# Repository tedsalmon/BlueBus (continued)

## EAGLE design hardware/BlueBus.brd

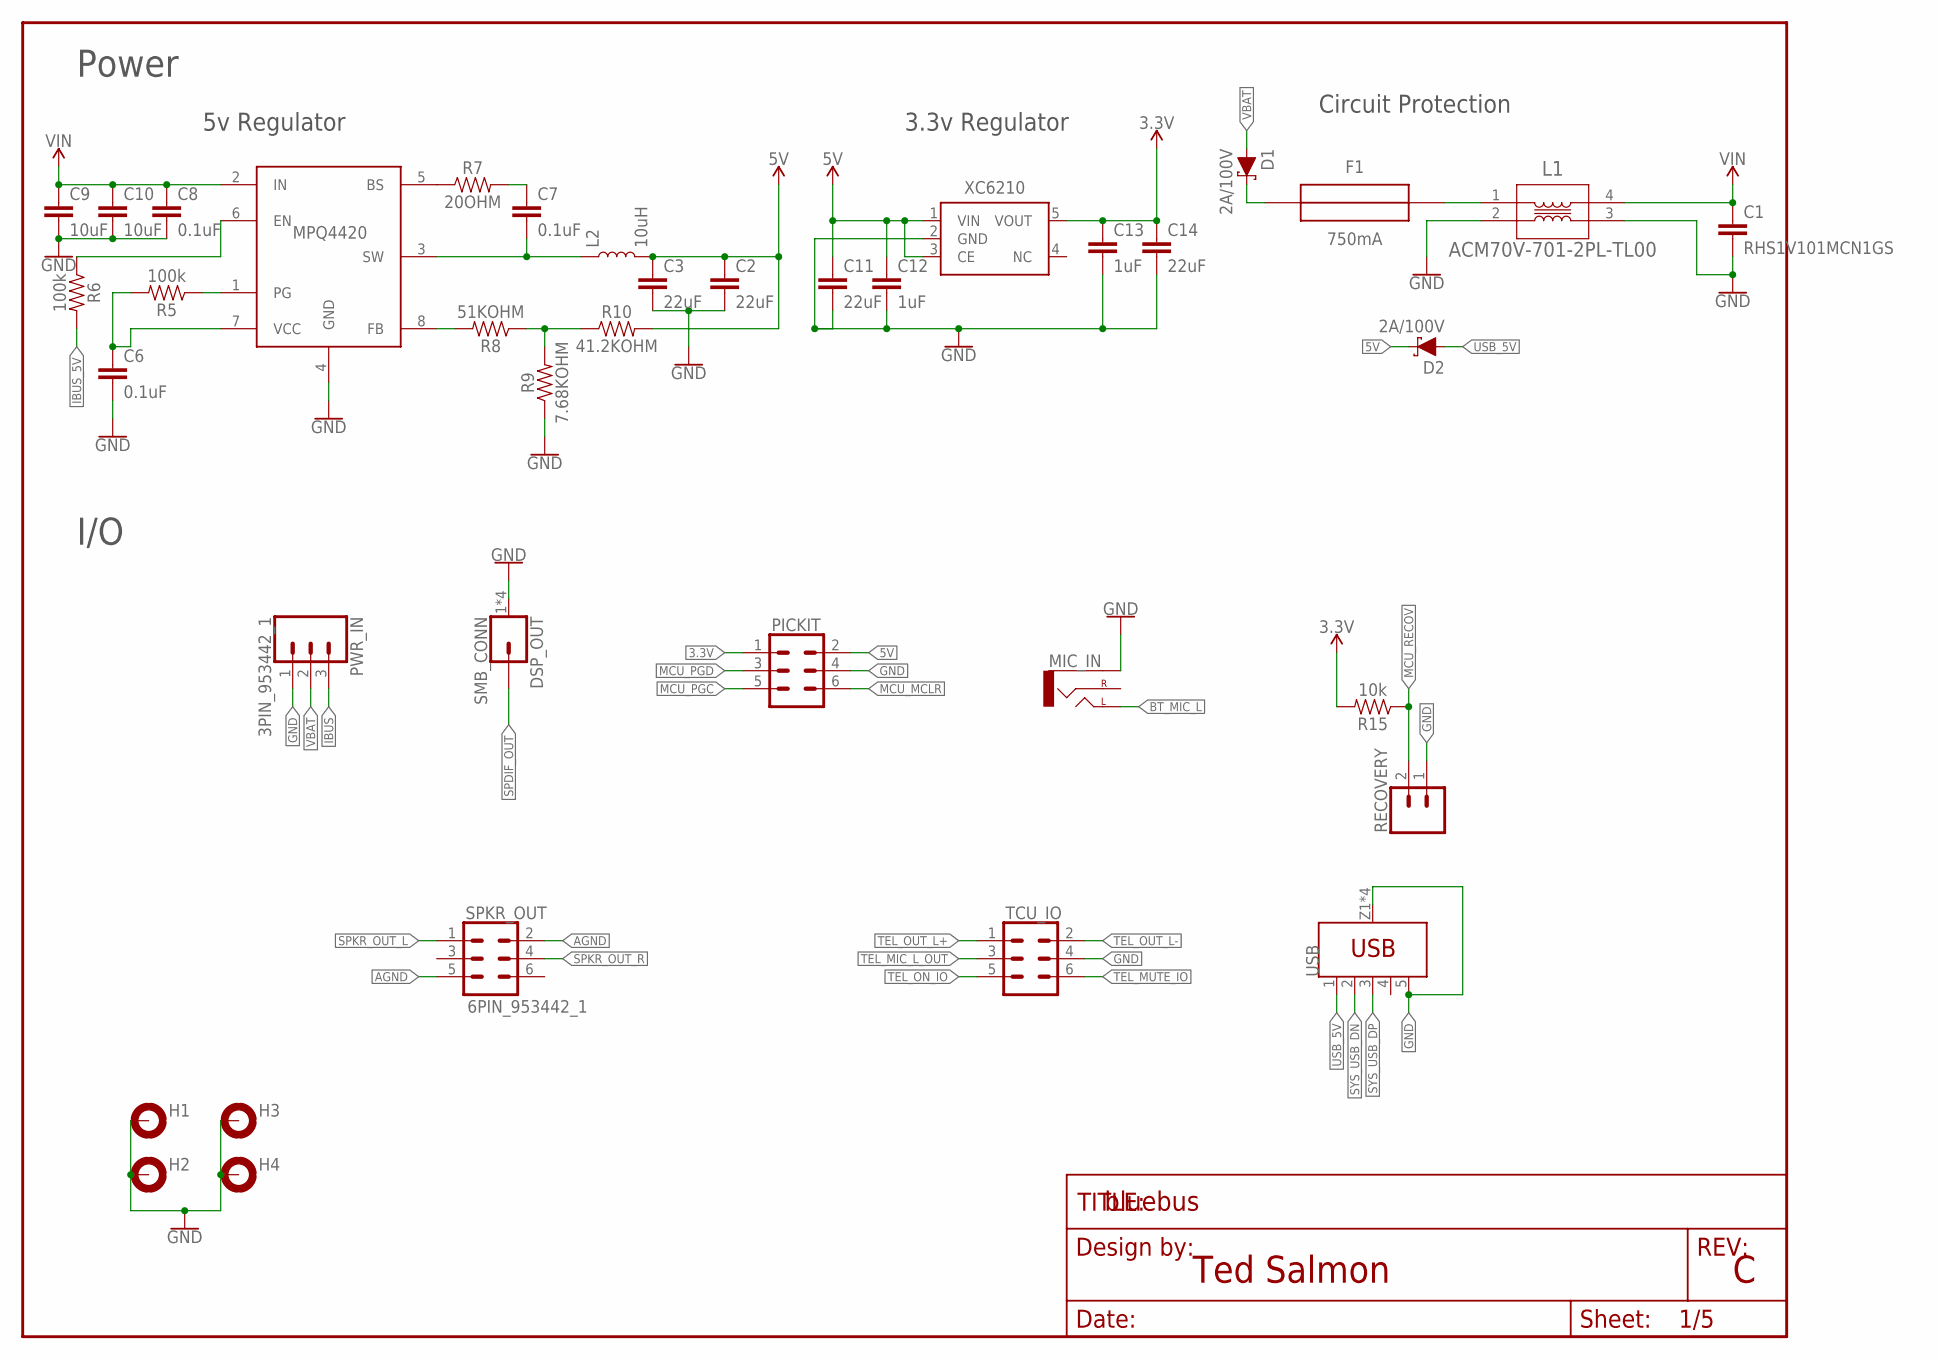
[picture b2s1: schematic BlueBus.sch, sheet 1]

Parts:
C1: RHS1V101MCN1GS
C2, C3, C11, C14: 22uF; 0805
C6, C7, C8: 0.1uF; 0805
C9, C10: 10uF; 1206
C12, C13: 1uF; 0805
D1, D2: 2A/100V; SOD123
DSP_OUT: SMB_CONN; MOLEX_SMB
F1: 750mA; LITTLEFUSE
FRAME1: FRAME-LETTER; DUMMY
H1, H2, H3, H4: 2,2-PAD; 2.2-PAD
L1: ACM70V-701-2PL-TL00
L2: 10uH; MPL-SE5040
MIC_IN: AUDIO-CUI-SJ-3523-SMT; AUDIO-CUI-SJ-352X-SMT
MPQ4420: MPQ4420; TSOT23-8
PICKIT: 6PIN_JUMPER; 2X3
PWR_IN: 3PIN_953442_1; TE_MQS_3PIN
R5, R6: 100k; 0805
R7: 20OHM; 0805
R8: 51KOHM; 0805
R9: 7.68KOHM; 0805
R10: 41.2KOHM; 0805
R15: 10k; 0805
RECOVERY: 2PIN_JUMPER; 1X02
SPKR_OUT: 6PIN_953442_1; TE_MQS_6PIN
TCU_IO: 6PIN_5_103166_1; TE_AMPMODU_6_PIN
USB: USB_WURTH_629105150521; 629105150521
XC6210: XC6210SOT25; SOT23-5

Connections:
3.3V: C13.1, C14.1, PICKIT.1, R15.2, XC6210.5 (VOUT); also elsewhere on the board
5V: C2.1, C3.1, C11.1, C12.1, D2.C, L2.2, PICKIT.2, R10.2, XC6210.1 (VIN), XC6210.3 (CE); also elsewhere on the board
5VREG_BS: MPQ4420.5 (BS), R7.1
5VREG_BS_CAP: C7.1, R7.2
5VREG_EN: MPQ4420.6 (EN), R6.1
5VREG_FB: MPQ4420.8 (FB), R8.2
5VREG_FB_T: R8.1, R9.2, R10.1
5VREG_PG: MPQ4420.1 (PG), R5.1
5VREG_SW: C7.2, L2.1, MPQ4420.3 (SW)
5VREG_VCC: C6.1, MPQ4420.7 (VCC), R5.2
AGND: SPKR_OUT.2, SPKR_OUT.5; also elsewhere on the board
BT_MIC_L: MIC_IN.TIP (LEFT); also elsewhere on the board
GND: C1.2, C2.2, C3.2, C6.2, C8.2, C9.2, C10.2, C11.2, C12.2, C13.2, C14.2, DSP_OUT.1 (GND), DSP_OUT.2 (GND), DSP_OUT.3 (GND), DSP_OUT.4 (GND), H1.B2.2, H2.B2.2, H3.B2.2, H4.B2.2, L1.2, L1.3, MIC_IN.SLEEVE, MPQ4420.4 (GND), PICKIT.4, PWR_IN.1, R9.1, RECOVERY.1, TCU_IO.4, USB.5 (GND), USB.Z1 (SHIELD), USB.Z2 (SHIELD), USB.Z3 (SHIELD), USB.Z4 (SHIELD), XC6210.2 (GND); also elsewhere on the board
IBUS: PWR_IN.3; also elsewhere on the board
IBUS_5V: R6.2; also elsewhere on the board
MCU_MCLR: PICKIT.6; also elsewhere on the board
MCU_PGC: PICKIT.5; also elsewhere on the board
MCU_PGD: PICKIT.3; also elsewhere on the board
MCU_RECOV: R15.1, RECOVERY.2; also elsewhere on the board
SPDIF_OUT: DSP_OUT.P$1 (1); also elsewhere on the board
SPKR_OUT_L: SPKR_OUT.1; also elsewhere on the board
SPKR_OUT_R: SPKR_OUT.4; also elsewhere on the board
SYS_USB_DN: USB.2 (D-); also elsewhere on the board
SYS_USB_DP: USB.3 (D+); also elsewhere on the board
TEL_MIC_L_OUT: TCU_IO.3; also elsewhere on the board
TEL_MUTE_IO: TCU_IO.6; also elsewhere on the board
TEL_ON_IO: TCU_IO.5; also elsewhere on the board
TEL_OUT_L+: TCU_IO.1; also elsewhere on the board
TEL_OUT_L-: TCU_IO.2; also elsewhere on the board
USB_5V: D2.A, USB.1 (VBUS)
VBAT: D1.A, PWR_IN.2
VBAT_DIODE: D1.C, F1.IN (OUT)
VBAT_FUSE: F1.OUT (IN), L1.1
VIN: C1.1, C8.1, C9.1, C10.1, L1.4, MPQ4420.2 (IN); also elsewhere on the board

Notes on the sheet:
Ted Salmon
Power
I/O
3.3v Regulator
5v Regulator
Circuit Protection

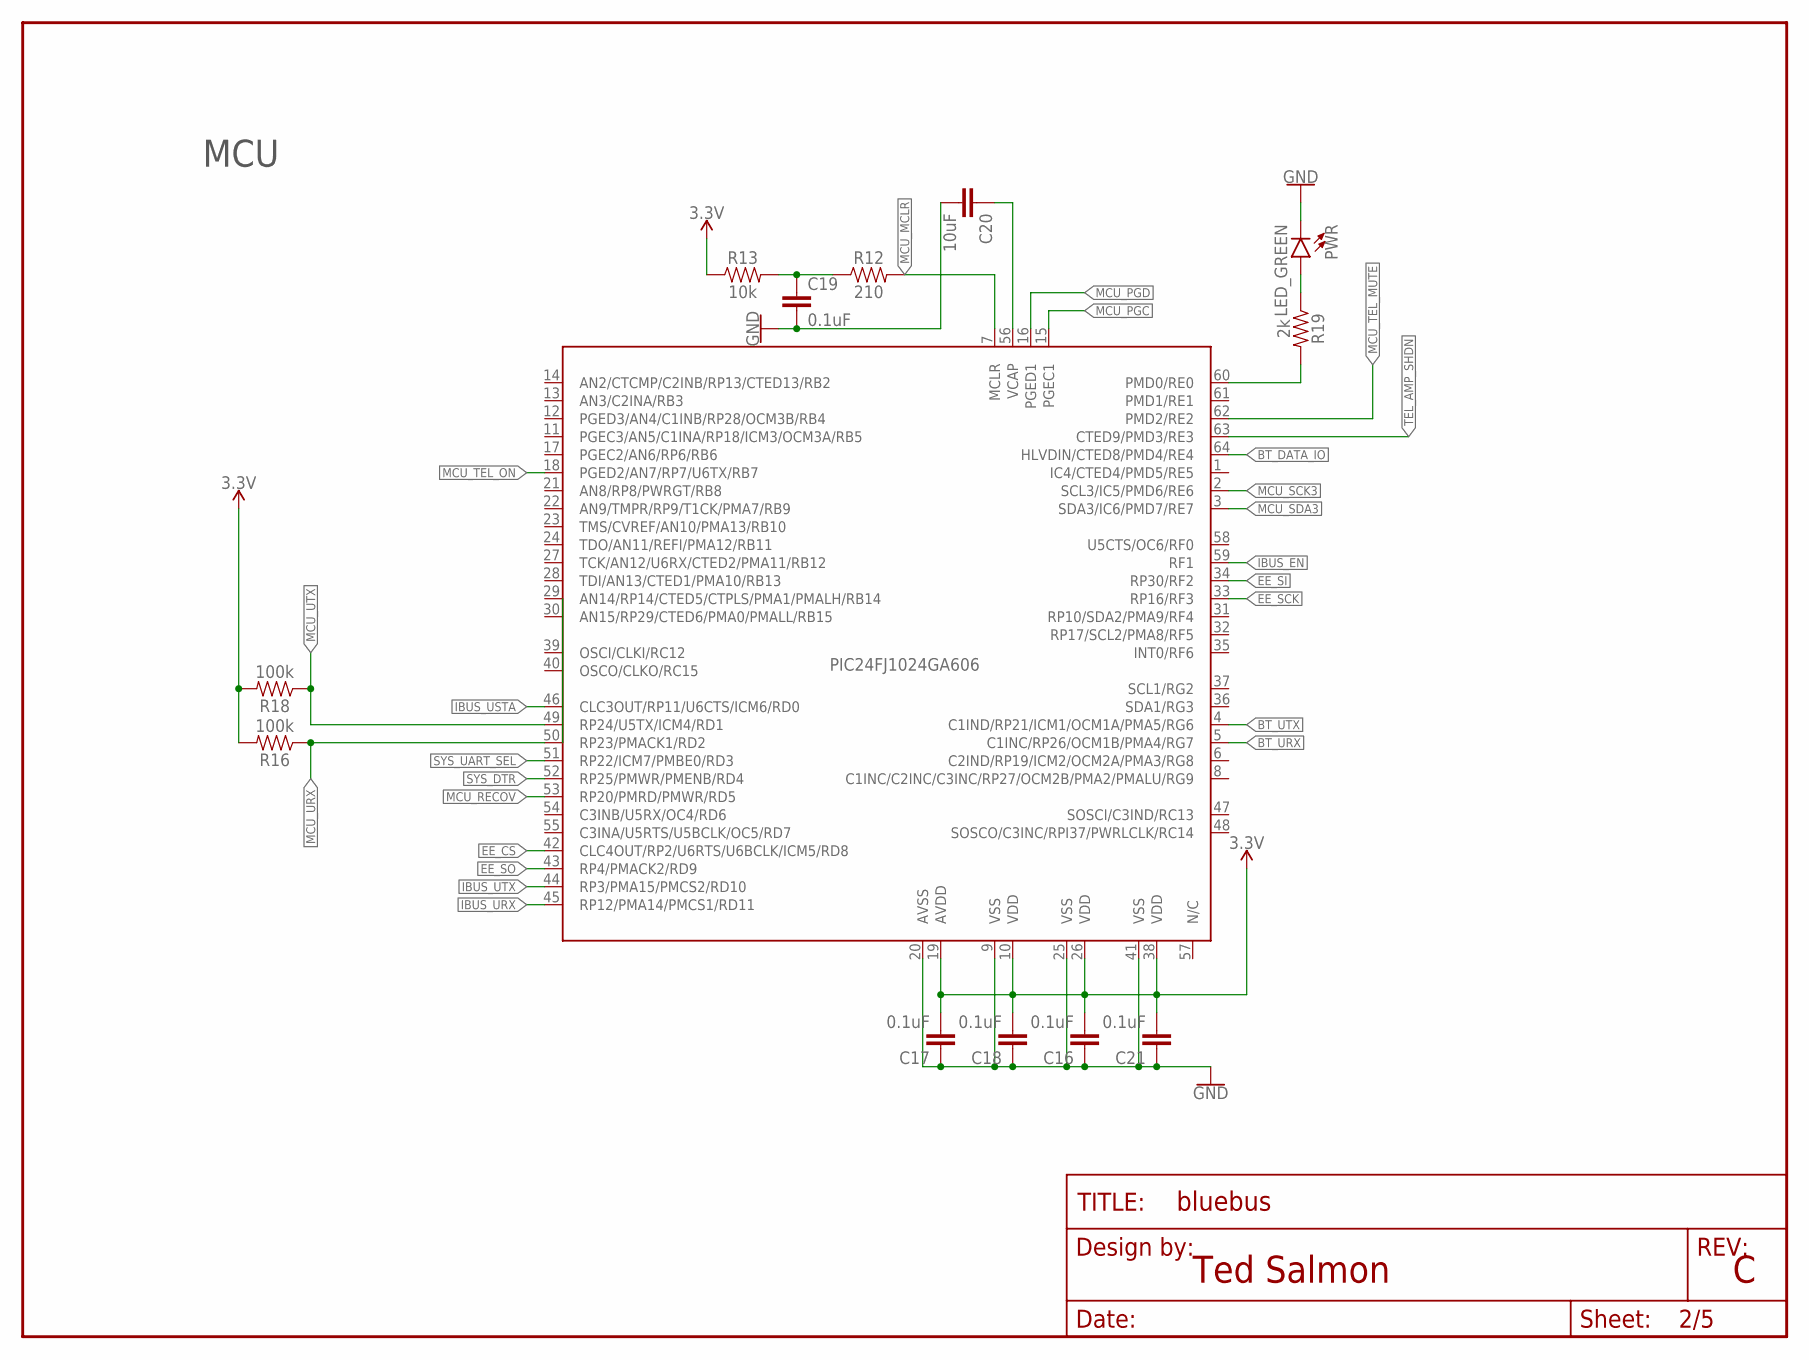
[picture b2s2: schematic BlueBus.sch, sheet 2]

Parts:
C16, C17, C18, C19, C21: 0.1uF; 0805
C20: 10uF; 0805
FRAME2: FRAME-LETTER; DUMMY
PIC24FJ1024GA606: PIC24FJ1024GA606; TQFP64
PWR: LED_GREEN; LED-0805
R12: 210; 0805
R13: 10k; 0805
R16, R18: 100k; 0805
R19: 2k; 0805

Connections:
3.3V: C16.2, C17.2, C18.2, C21.2, PIC24FJ1024GA606.10 (VDD), PIC24FJ1024GA606.19 (AVDD), PIC24FJ1024GA606.26 (VDD), PIC24FJ1024GA606.38 (VDD), R13.1, R16.2, R18.2; also elsewhere on the board
BT_DATA_IO: PIC24FJ1024GA606.64 (HLVDIN/CTED8/PMD4/RE4); also elsewhere on the board
BT_URX: PIC24FJ1024GA606.5 (C1INC/RP26/OCM1B/PMA4/RG7); also elsewhere on the board
BT_UTX: PIC24FJ1024GA606.4 (C1IND/RP21/ICM1/OCM1A/PMA5/RG6); also elsewhere on the board
EE_CS: PIC24FJ1024GA606.42 (CLC4OUT/RP2/U6RTS/U6BCLK/ICM5/RD8); also elsewhere on the board
EE_SCK: PIC24FJ1024GA606.33 (RP16/RF3); also elsewhere on the board
EE_SI: PIC24FJ1024GA606.34 (RP30/RF2); also elsewhere on the board
EE_SO: PIC24FJ1024GA606.43 (RP4/PMACK2/RD9); also elsewhere on the board
GND: C16.1, C17.1, C18.1, C19.2, C20.2, C21.1, PIC24FJ1024GA606.9 (VSS), PIC24FJ1024GA606.20 (AVSS), PIC24FJ1024GA606.25 (VSS), PIC24FJ1024GA606.41 (VSS), PWR.- (C); also elsewhere on the board
IBUS_EN: PIC24FJ1024GA606.59 (RF1); also elsewhere on the board
IBUS_URX: PIC24FJ1024GA606.45 (RP12/PMA14/PMCS1/RD11); also elsewhere on the board
IBUS_USTA: PIC24FJ1024GA606.46 (CLC3OUT/RP11/U6CTS/ICM6/RD0); also elsewhere on the board
IBUS_UTX: PIC24FJ1024GA606.44 (RP3/PMA15/PMCS2/RD10); also elsewhere on the board
MCU_MCLR: PIC24FJ1024GA606.7 (MCLR), R12.2; also elsewhere on the board
MCU_MCLR_RES: C19.1, R12.1, R13.2
MCU_ON_LED: PIC24FJ1024GA606.60 (PMD0/RE0), R19.2
MCU_ON_LED_RES: PWR.+ (A), R19.1
MCU_PGC: PIC24FJ1024GA606.15 (PGEC1); also elsewhere on the board
MCU_PGD: PIC24FJ1024GA606.16 (PGED1); also elsewhere on the board
MCU_RECOV: PIC24FJ1024GA606.53 (RP20/PMRD/PMWR/RD5); also elsewhere on the board
MCU_SCK3: PIC24FJ1024GA606.2 (SCL3/IC5/PMD6/RE6); also elsewhere on the board
MCU_SDA3: PIC24FJ1024GA606.3 (SDA3/IC6/PMD7/RE7); also elsewhere on the board
MCU_TEL_MUTE: PIC24FJ1024GA606.62 (PMD2/RE2); also elsewhere on the board
MCU_TEL_ON: PIC24FJ1024GA606.18 (PGED2/AN7/RP7/U6TX/RB7); also elsewhere on the board
MCU_URX: PIC24FJ1024GA606.50 (RP23/PMACK1/RD2), R16.1; also elsewhere on the board
MCU_UTX: PIC24FJ1024GA606.49 (RP24/U5TX/ICM4/RD1), R18.1; also elsewhere on the board
MCU_VCAP: C20.1, PIC24FJ1024GA606.56 (VCAP)
SYS_DTR: PIC24FJ1024GA606.52 (RP25/PMWR/PMENB/RD4); also elsewhere on the board
SYS_UART_SEL: PIC24FJ1024GA606.51 (RP22/ICM7/PMBE0/RD3); also elsewhere on the board
TEL_AMP_SHDN: PIC24FJ1024GA606.63 (CTED9/PMD3/RE3); also elsewhere on the board

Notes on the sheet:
Ted Salmon
MCU

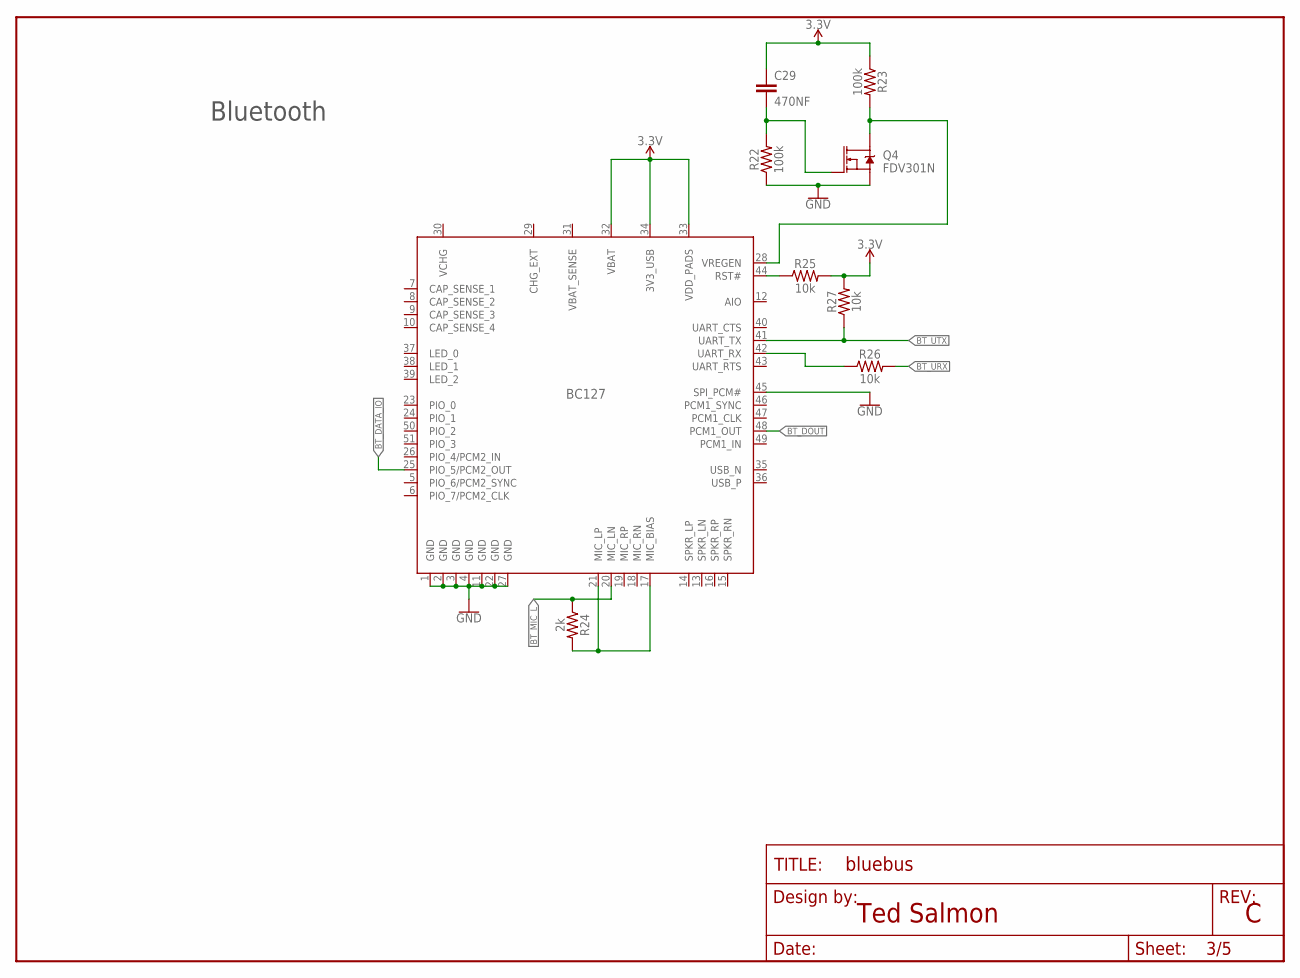
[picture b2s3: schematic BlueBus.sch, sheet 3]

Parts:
BC127: BC127
C29: 470NF; 0805
FRAME4: FRAME-LETTER; DUMMY
Q4: FDV301N; SOT-23
R22, R23: 100k; 0805
R24: 2k; 0805
R25, R26, R27: 10k; 0805

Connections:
3.3V: BC127.32 (VBAT), BC127.33 (VDD_PADS), BC127.34 (3V3_USB), C29.1, R23.1, R25.2, R27.2; also elsewhere on the board
BT_DATA_IO: BC127.25 (PIO_5/PCM2_OUT); also elsewhere on the board
BT_DOUT: BC127.48 (PCM1_OUT); also elsewhere on the board
BT_MIC_BIAS: BC127.17 (MIC_BIAS), BC127.21 (MIC_LP), R24.2
BT_MIC_L: BC127.20 (MIC_LN), R24.1; also elsewhere on the board
BT_RST: BC127.44 (RST#), R25.1
BT_URX: R26.2; also elsewhere on the board
BT_URX_RES: BC127.42 (UART_RX), R26.1
BT_UTX: BC127.41 (UART_TX), R27.1; also elsewhere on the board
BT_VREGEN: BC127.28 (VREGEN), Q4.3 (D), R23.2
BT_VREGEN_CAP_GATE: C29.2, Q4.1 (G), R22.2
CHG_EXT: BC127.29 (CHG_EXT)
GND: BC127.1 (GND), BC127.2 (GND), BC127.3 (GND), BC127.4 (GND), BC127.11 (GND), BC127.22 (GND), BC127.27 (GND), BC127.45 (SPI_PCM#), Q4.2 (S), R22.1; also elsewhere on the board
VBAT_SENSE: BC127.31 (VBAT_SENSE)
VCHG: BC127.30 (VCHG)

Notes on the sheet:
Bluetooth
Ted Salmon

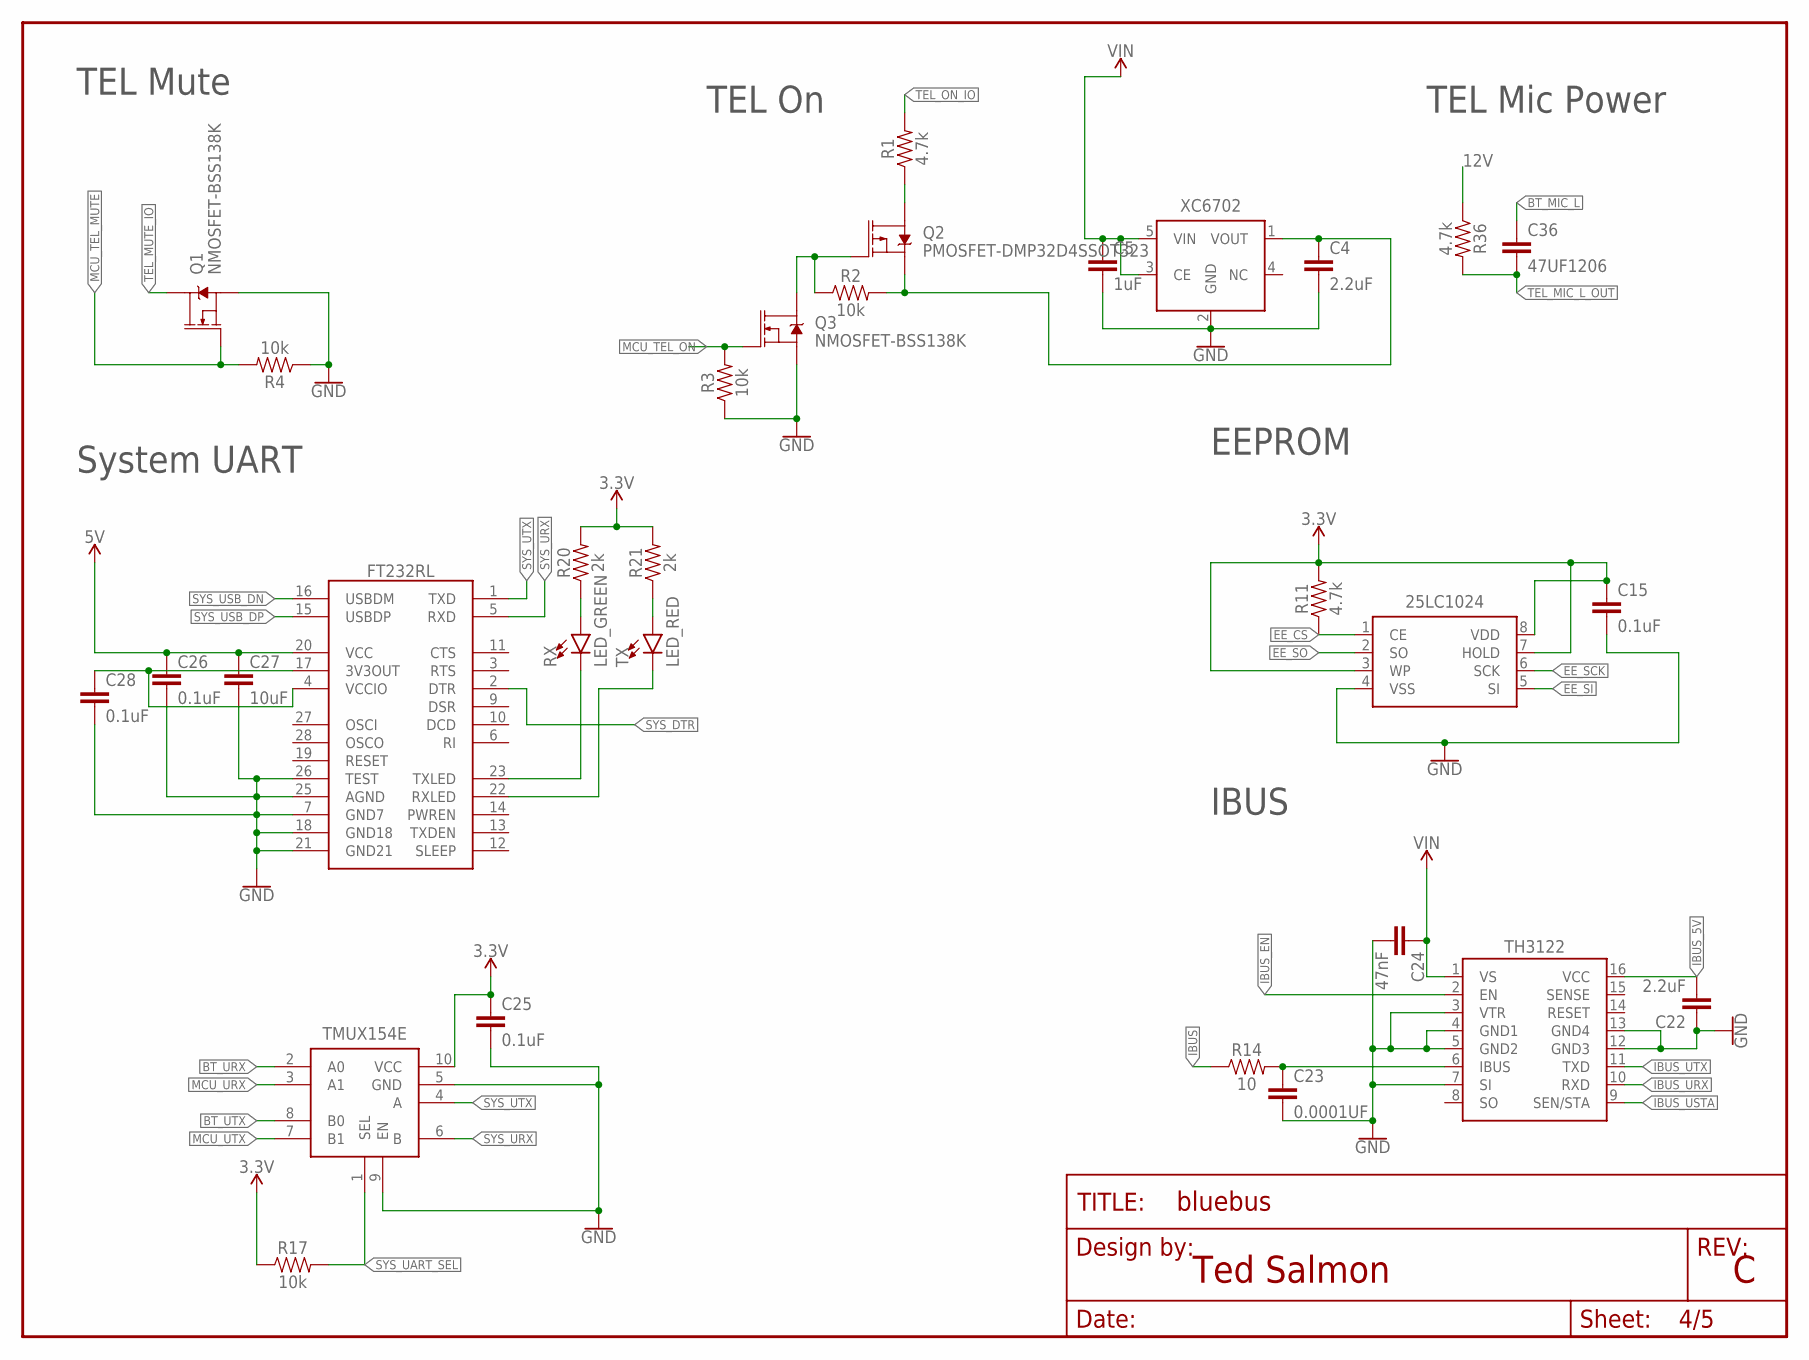
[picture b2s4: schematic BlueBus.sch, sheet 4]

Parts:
25LC1024: 25LC1024; SOIJ-8
C4, C22: 2.2uF; 0805
C5: 1uF; 0805
C15, C25, C26, C28: 0.1uF; 0805
C23: 0.0001UF; 0805
C24: 47nF; 0805
C27: 10uF; 0805
C36: 47UF1206; 1206
FRAME3: FRAME-LETTER; DUMMY
FT232RL: FT232RL; SSOP28
Q1, Q3: NMOSFET-BSS138K; SOT-23
Q2: PMOSFET-DMP32D4SSOT323; SOT323
R1, R11, R36: 4.7k; 0805
R2, R3, R4, R17: 10k; 0805
R14: 10; 0805
R20, R21: 2k; 0805
RX: LED_GREEN; LED-0805
TH3122: TH3122.4; SOIC16DF
TMUX154E: TMUX154E; VSSOP10
TX: LED_RED; LED-0805
XC6702: XC6702DC018PR-G; SOT-89-5

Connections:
3.3V: 25LC1024.3 (WP), 25LC1024.7 (HOLD), 25LC1024.8 (VDD), C15.1, C25.1, R11.2, R17.1, R20.2, R21.2, TMUX154E.10 (VCC); also elsewhere on the board
5V: C26.1, C27.1, FT232RL.20 (VCC); also elsewhere on the board
12V: C4.1, Q2.2 (S), R2.2, R36.1, XC6702.1 (VOUT)
BT_MIC_L: C36.1; also elsewhere on the board
BT_URX: TMUX154E.2 (A0); also elsewhere on the board
BT_UTX: TMUX154E.8 (B0); also elsewhere on the board
EE_CS: 25LC1024.1 (CE), R11.1; also elsewhere on the board
EE_SCK: 25LC1024.6 (SCK); also elsewhere on the board
EE_SI: 25LC1024.5 (SI); also elsewhere on the board
EE_SO: 25LC1024.2 (SO); also elsewhere on the board
GND: 25LC1024.4 (VSS), C4.2, C5.2, C15.2, C22.1, C23.2, C24.2, C25.2, C26.2, C27.2, C28.2, FT232RL.7 (GND7), FT232RL.18 (GND18), FT232RL.21 (GND21), FT232RL.25 (AGND), FT232RL.26 (TEST), Q1.2 (S), Q3.2 (S), R3.1, R4.1, TH3122.3 (VTR), TH3122.4 (GND1), TH3122.5 (GND2), TH3122.7 (SI), TH3122.12 (GND3), TH3122.13 (GND4), TMUX154E.5 (GND), TMUX154E.9 (EN), XC6702.2 (GND); also elsewhere on the board
IBUS: R14.1; also elsewhere on the board
IBUS_5V: C22.2, TH3122.16 (VCC); also elsewhere on the board
IBUS_EN: TH3122.2 (EN); also elsewhere on the board
IBUS_FILT: C23.1, R14.2, TH3122.6 (IBUS)
IBUS_URX: TH3122.10 (RXD); also elsewhere on the board
IBUS_USTA: TH3122.9 (SEN/STA); also elsewhere on the board
IBUS_UTX: TH3122.11 (TXD); also elsewhere on the board
MCU_TEL_MUTE: Q1.1 (G), R4.2; also elsewhere on the board
MCU_TEL_ON: Q3.1 (G), R3.2; also elsewhere on the board
MCU_URX: TMUX154E.3 (A1); also elsewhere on the board
MCU_UTX: TMUX154E.7 (B1); also elsewhere on the board
RX_LED: FT232RL.23 (TXLED), RX.- (C)
RX_LED_RES: R20.1, RX.+ (A)
SYS_3V3: C28.1, FT232RL.4 (VCCIO), FT232RL.17 (3V3OUT)
SYS_DTR: FT232RL.2 (DTR); also elsewhere on the board
SYS_UART_SEL: R17.2, TMUX154E.1 (SEL); also elsewhere on the board
SYS_URX: FT232RL.5 (RXD), TMUX154E.6 (B)
SYS_USB_DN: FT232RL.16 (USBDM); also elsewhere on the board
SYS_USB_DP: FT232RL.15 (USBDP); also elsewhere on the board
SYS_UTX: FT232RL.1 (TXD), TMUX154E.4 (A)
TEL_MIC_L_OUT: C36.2, R36.2; also elsewhere on the board
TEL_MUTE_IO: Q1.3 (D); also elsewhere on the board
TEL_ON: Q2.3 (D), R1.1
TEL_ON_EN: Q2.1 (G), Q3.3 (D), R2.1
TEL_ON_IO: R1.2; also elsewhere on the board
TX_LED: FT232RL.22 (RXLED), TX.- (C)
TX_LED_RES: R21.1, TX.+ (A)
VIN: C5.1, C24.1, TH3122.1 (VS), XC6702.3 (CE), XC6702.5 (VIN); also elsewhere on the board

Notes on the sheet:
Ted Salmon
IBUS
EEPROM
TEL On
TEL Mute
TEL Mic Power
System UART

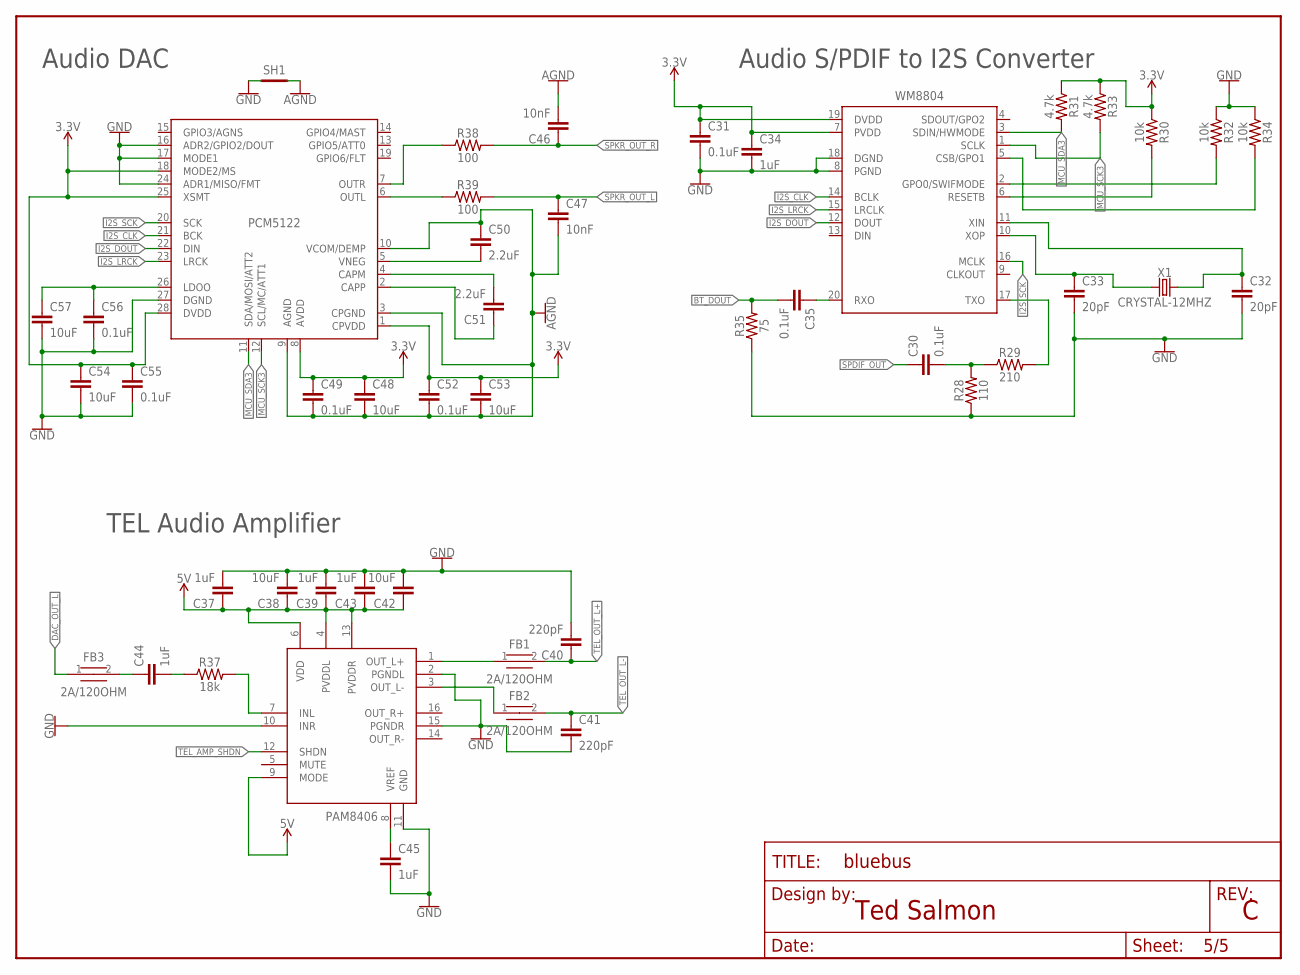
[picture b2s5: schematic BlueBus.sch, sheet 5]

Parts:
C30, C31, C35, C49, C52, C55, C56: 0.1uF; 0805
C32, C33: 20pF; 0805
C34, C37, C39, C43, C44, C45: 1uF; 0805
C38, C42, C48, C53, C54, C57: 10uF; 0805
C40, C41: 220pF; 0805
C46, C47: 10nF; 0805
C50, C51: 2.2uF; 0805
FB1, FB2, FB3: 2A/120OHM; 0805
FRAME5: FRAME-LETTER; DUMMY
PAM8406: PAM8406; SOP-16
PCM5122: PCM5122; TSSOP28
R28: 110; 0805
R29: 210; 0805
R30, R32, R34: 10k; 0805
R31, R33: 4.7k; 0805
R35: 75; 0805
R37: 18k; 0805
R38, R39: 100; 0805
SH1: SHORTT5; SHORT_TOP-50
WM8804: WM8804; SSOP20
X1: CRYSTAL-12MHZ; HC49

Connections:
3.3V: C31.1, C34.1, C48.1, C49.1, C52.1, C53.1, C54.1, C55.1, PCM5122.1 (CPVDD), PCM5122.8 (AVDD), PCM5122.18 (MODE2/MS), PCM5122.25 (XSMT), PCM5122.28 (DVDD), R30.1, R31.1, R33.1, WM8804.7 (PVDD), WM8804.19 (DVDD); also elsewhere on the board
5V: C37.1, C38.1, C39.1, C42.1, C43.1, PAM8406.4 (PVDDL), PAM8406.6 (VDD), PAM8406.9 (MODE), PAM8406.13 (PVDDR); also elsewhere on the board
AGND: C46.2, C47.2, C48.2, C49.2, C50.1, C52.2, C53.2, PCM5122.3 (CPGND), PCM5122.9 (AGND), PCM5122.10 (VCOM/DEMP), SH1.2; also elsewhere on the board
BT_DOUT: C35.2, R35.2; also elsewhere on the board
DAC_CAPM: C51.2, PCM5122.4 (CAPM)
DAC_CAPP: C51.1, PCM5122.2 (CAPP)
DAC_LDOO: C56.1, C57.1, PCM5122.26 (LDOO)
DAC_OUT_L: FB3.1, PCM5122.6 (OUTL), R39.1
DAC_OUT_R: PCM5122.7 (OUTR), R38.1
DAC_VNEG: C50.2, PCM5122.5 (VNEG)
GND: C31.2, C32.2, C33.2, C34.2, C37.2, C38.2, C39.2, C40.2, C41.2, C42.2, C43.2, C45.2, C54.2, C55.2, C56.2, C57.2, PAM8406.2 (PGNDL), PAM8406.10 (INR), PAM8406.11 (GND), PAM8406.15 (PGNDR), PCM5122.16 (ADR2/GPIO2/DOUT), PCM5122.17 (MODE1), PCM5122.24 (ADR1/MISO/FMT), PCM5122.27 (DGND), R28.1, R32.1, R34.1, R35.1, SH1.1, WM8804.8 (PGND), WM8804.18 (DGND); also elsewhere on the board
I2S_CLK: PCM5122.21 (BCK), WM8804.14 (BCLK)
I2S_DOUT: PCM5122.22 (DIN), WM8804.12 (DOUT)
I2S_LRCK: PCM5122.23 (LRCK), WM8804.15 (LRCLK)
I2S_SCK: PCM5122.20 (SCK), WM8804.16 (MCLK)
MCU_SCK3: PCM5122.12 (SCL/MC/ATT1), R33.2, WM8804.1 (SCLK); also elsewhere on the board
MCU_SDA3: PCM5122.11 (SDA/MOSI/ATT2), R31.2, WM8804.3 (SDIN/HWMODE); also elsewhere on the board
SPDIF_OUT: C30.1; also elsewhere on the board
SPDIF_RX: C35.1, WM8804.20 (RXO)
SPKR_OUT_L: C47.1, R39.2; also elsewhere on the board
SPKR_OUT_R: C46.1, R38.2; also elsewhere on the board
TEL_AMP_IN: C44.1, FB3.2
TEL_AMP_INL: PAM8406.7 (INL), R37.2
TEL_AMP_INL_CAP_RES: C44.2, R37.1
TEL_AMP_OUT_L+: FB1.1, PAM8406.1 (OUT_L+)
TEL_AMP_OUT_L-: FB2.1, PAM8406.3 (OUT_L-)
TEL_AMP_SHDN: PAM8406.12 (SHDN); also elsewhere on the board
TEL_AMP_VREF: C45.1, PAM8406.8 (VREF)
TEL_OUT_L+: C40.1, FB1.2; also elsewhere on the board
TEL_OUT_L-: C41.1, FB2.2; also elsewhere on the board
WM_CSB: R34.2, WM8804.5 (CSB/GPO1)
WM_GPO0: R32.2, WM8804.2 (GPO0/SWIFMODE)
WM_RESETB: R30.2, WM8804.6 (RESETB)
WM_SPDIF_TX_RES: R29.2, WM8804.17 (TXO)
WM_SPDIF_TX_RES2: C30.2, R28.2, R29.1
WM_XIN: C32.1, WM8804.11 (XIN), X1.2
WM_XOP: C33.1, WM8804.10 (XOP), X1.1

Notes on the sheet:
Audio DAC
Audio S/PDIF to I2S Converter
TEL Audio Amplifier
Ted Salmon

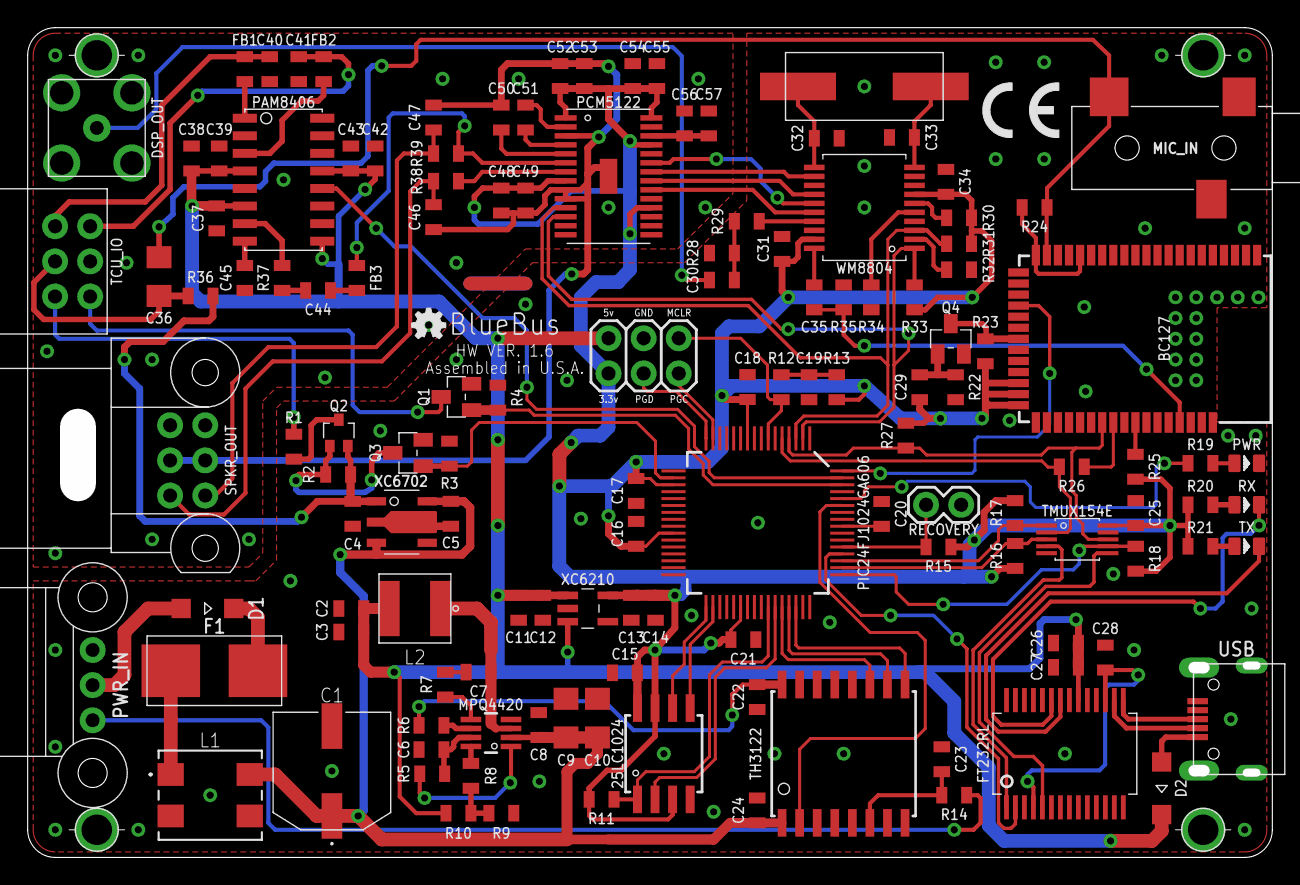
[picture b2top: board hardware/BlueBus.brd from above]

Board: 2 copper layers, 90.0 x 60.0 mm, 144 parts (0 on the bottom side), 99 nets.

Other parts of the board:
CE: CE-4MM
OSHW: OSHW-LOGO-MINI

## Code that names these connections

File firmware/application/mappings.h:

/*
 * IO Mappings for the PIC24
 */
#ifndef IO_MAPPINGS_H
#define IO_MAPPINGS_H
#define IBUS_UART_MODULE 1
#define IBUS_UART_RX_PRIORITY 7
#define IBUS_UART_TX_PRIORITY 5
#define IBUS_UART_RX_PIN_MODE TRISDbits.TRISD11
#define IBUS_UART_RX_PIN LATDbits.LATD11
#define IBUS_UART_RX_RPIN 12
#define IBUS_UART_TX_PIN_MODE TRISDbits.TRISD10
#define IBUS_UART_TX_PIN LATDbits.LATD10
#define IBUS_UART_TX_RPIN 3
#define IBUS_UART_STATUS_MODE TRISDbits.TRISD0
#define IBUS_UART_STATUS PORTDbits.RD0


#define BT_UART_MODULE 2
#define BT_UART_RX_PRIORITY 6
#define BT_UART_TX_PRIORITY 5
#define BT_UART_RX_PIN_MODE TRISGbits.TRISG6
#define BT_UART_RX_PIN LATGbits.LATG6
#define BT_UART_RX_RPIN 21
#define BT_UART_TX_PIN_MODE TRISGbits.TRISG7
#define BT_UART_TX_PIN LATGbits.LATG7
#define BT_UART_TX_RPIN 26

#define SYSTEM_UART_MODULE 3
#define SYSTEM_UART_RX_PRIORITY 3
#define SYSTEM_UART_TX_PRIORITY 4
#define SYSTEM_UART_RX_PIN_MODE TRISDbits.TRISD2
#define SYSTEM_UART_RX_PIN LATDbits.LATD2
#define SYSTEM_UART_RX_RPIN 23
#define SYSTEM_UART_TX_PIN_MODE TRISDbits.TRISD1
#define SYSTEM_UART_TX_PIN LATDbits.LATD1
#define SYSTEM_UART_TX_RPIN 24

#define EEPROM_SPI_MODULE 1
#define EEPROM_CS_PIN PORTDbits.RD8
#define EEPROM_CS_IO_MODE TRISDbits.TRISD8
#define EEPROM_SCK_RPIN 16
#define EEPROM_SDI_PIN_MODE TRISDbits.TRISD9
#define EEPROM_SDI_RPIN 4
#define EEPROM_SDO_RPIN 30

#define BOARD_VERSION_ONE 0
#define BOARD_VERSION_TWO 1

#define BOARD_VERSION_MODE TRISGbits.TRISG8
#define BOARD_VERSION_STATUS PORTGbits.RG8
#define BOARD_VERSION_PD IOCPDGbits.IOCPDG8

#define BT_BOOT_TYPE_MODE TRISEbits.TRISE1
#define BT_BOOT_TYPE LATEbits.LATE1

#define BT_DATA_SEL_MODE TRISEbits.TRISE4
#define BT_DATA_SEL LATEbits.LATE4

#define BT_MFB_MODE TRISEbits.TRISE5
#define BT_MFB LATEbits.LATE5

#define BT_RST_MODE TRISFbits.TRISF0
#define BT_RST LATFbits.LATF0

#define I2C3_SDA_MODE TRISEbits.TRISE7
#define I2C3_SDA LATEbits.LATE7
#define I2C3_SDA_STATUS PORTEbits.RE7

#define I2C3_SCL_MODE TRISEbits.TRISE6
#define I2C3_SCL LATEbits.LATE6
#define I2C3_SCL_STATUS PORTEbits.RE6

#define ON_LED_MODE TRISEbits.TRISE0
#define ON_LED LATEbits.LATE0

#define UART_SEL_BT 0
#define UART_SEL_MCU 1
#define UART_SEL_MODE TRISDbits.TRISD3
#define UART_SEL LATDbits.LATD3

#define IVT_MODE INTCON2bits.AIVTEN
#define IVT_MODE_APP 1
#define IVT_MODE_BOOT 0

#define IBUS_EN_MODE TRISFbits.TRISF1
#define IBUS_EN_STATUS PORTFbits.RF1
#define IBUS_EN LATFbits.LATF1

#define PAM_SHDN_MODE TRISEbits.TRISE3
#define PAM_SHDN LATEbits.LATE3

#define SPDIF_RST_MODE TRISEbits.TRISE2
#define SPDIF_RST LATEbits.LATE2

#define SYS_DTR_MODE TRISDbits.TRISD4
#define SYS_DTR_STATUS PORTDbits.RD4

#define TEL_ON_MODE_V1 TRISBbits.TRISB7
#define TEL_ON_V1 LATBbits.LATB7

#define TEL_MUTE_MODE_V1 TRISEbits.TRISE2
#define TEL_MUTE_V1 LATEbits.LATE2

#define TEL_ON_MODE_V2 TRISFbits.TRISF5
#define TEL_ON_V2 LATFbits.LATF5

#define TEL_MUTE_MODE_V2 TRISFbits.TRISF4
#define TEL_MUTE_V2 LATFbits.LATF4

// UI Events
#define UI_EVENT_INITIATE_CONNECTION 96
#define UI_EVENT_CLOSE_CONNECTION 97
#define UI_EVENT_MAIN_DISPLAY_UPDATE 98
#define UI_EVENT_CLI_WRITE_BEFORE 99
#define UI_EVENT_CLI_WRITE_COMPLETE 100

#define FIRMWARE_VERSION_MAJOR 1
#define FIRMWARE_VERSION_MINOR 4
#define FIRMWARE_VERSION_PATCH 43

void TrapWait();
#endif /* IO_MAPPINGS_H */
